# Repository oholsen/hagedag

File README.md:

# hagedag
DIY lawn mower robot

## Testing

Run unit tests:

    poetry run pytest -s

Run simulation:

    poetry run python .\record.py

(Replay log file, should add fail safe detection ++):

    poetry run python .\record.py .\data\burned-motor.log

## TODO

* motor burned (one wheel was tangled in grass):
  * wifi connection delayed - commands and feedback
  * figure out why robot estimate wrongly turned and why it did not recover when moving "right"
  * fix: move control to robot, detect connection delays, ignore delayed information, timestamp from STM32, use timestamp from GPS

* high load on motor detection - possibly integrate and average
  * cut in STM or in control? Control, as will get to know what is going on?
  * STM will stop robot if communication errors, safe to cut in control.
  * different max for instantaneous and average load?
  * Simply stop when above threshold (instantaneous)

* robot stuck detection: anomaly on prediction and GPS
  * measure distance travelled over last 5 say on GPS and compare to integrated speed

* wifi delay detection
    * shorter timeout (1s/2s)
    * embed timeout in command
    * alert in GUI

* stop cutter outside fence?
* cutter stuck detection
* revs sensor on cutter

* slow down near fence
* keep estimating position with odometer only when no GPS fix -> higher uncertainty

* Fence
    * increase area behind garage
    * reduce fence area near stairs

* App robustness
    * restart GPS service when USB unavailable, also ntrip client fails badly? restart service should be ok...
    * properly stop all tasks, also controld connection, from PC app
    * program firmware with heartbeat on commands

Usability:
    * Don't make PC app always be on top: run GUI task in own thread?
    * PC/Web/mobile app framework: pyplot, JS, plotly-dash, ...
    * identify what goes wrong / status
    * restart e.g. line scan from current position?

* Tidy up app:
   * remove unused code

* move app to robot

* change direction of robot

* slow down near fence, speed up in the middle (may make crash prediction below unnecessary - if reducing heartbeat timeout in robot)
* keep going for large HDOP if far from fence
* use GPS hdop in tracking, figure out why HDOP is 0.5 when RTK
* looser cut-off on no RTK - either adjust error in GPS tracking (check out HDOP in RMC)
 - or - accept no GPS for a while - at least if heading is good and is not going to crash.
 estimate time to impact from last good RTK position?
BUT: also quicker than 5s heartbeat timeout, i.e. direct STOP command if about to crash and loose RTK 
* avoid going in circles on drifting GPS: HDOP -> tracker could solve that
* area filling - scan lines
* if HDOP high: alternative targets or wait for ok HDOP
* fence bump control: reverse out from fence

* automatic charging
* docking garage
* camera
* camera coverage of garden
* realsense - mapping, collision avoidance

Mission control dashboard
- map (draw AOI, speeds/behavior, move fence, path, density, ..., GPS/tracking error, heading error)
- system health: show currents, battery level
- (E)stop button
- Duration, Ah drawn (total, trip (since charge), button for reset trip charge), distance covered
- Mode: fence bump, lines, manual, manual override (temporarily)
- Manual controls
- Start mission - which mission
- app to monitor status, with notifications on issues

Analytics
- GPS/tracking precision
- Coverage
- Replay/show mission on map

Mapping
- find fence - show position on map with manual control - recorder mode....

Mission control
- run to area of "little" probability
- speed and cut speed as fn(x,y)
- avoid tail swinging out (reverse back out, put GPS above cutter and turn around cutter)
- estimate error based on odometry and GPS signal - keep on going if looses RTK
- TODO: check GPS error when stopped and no RTK

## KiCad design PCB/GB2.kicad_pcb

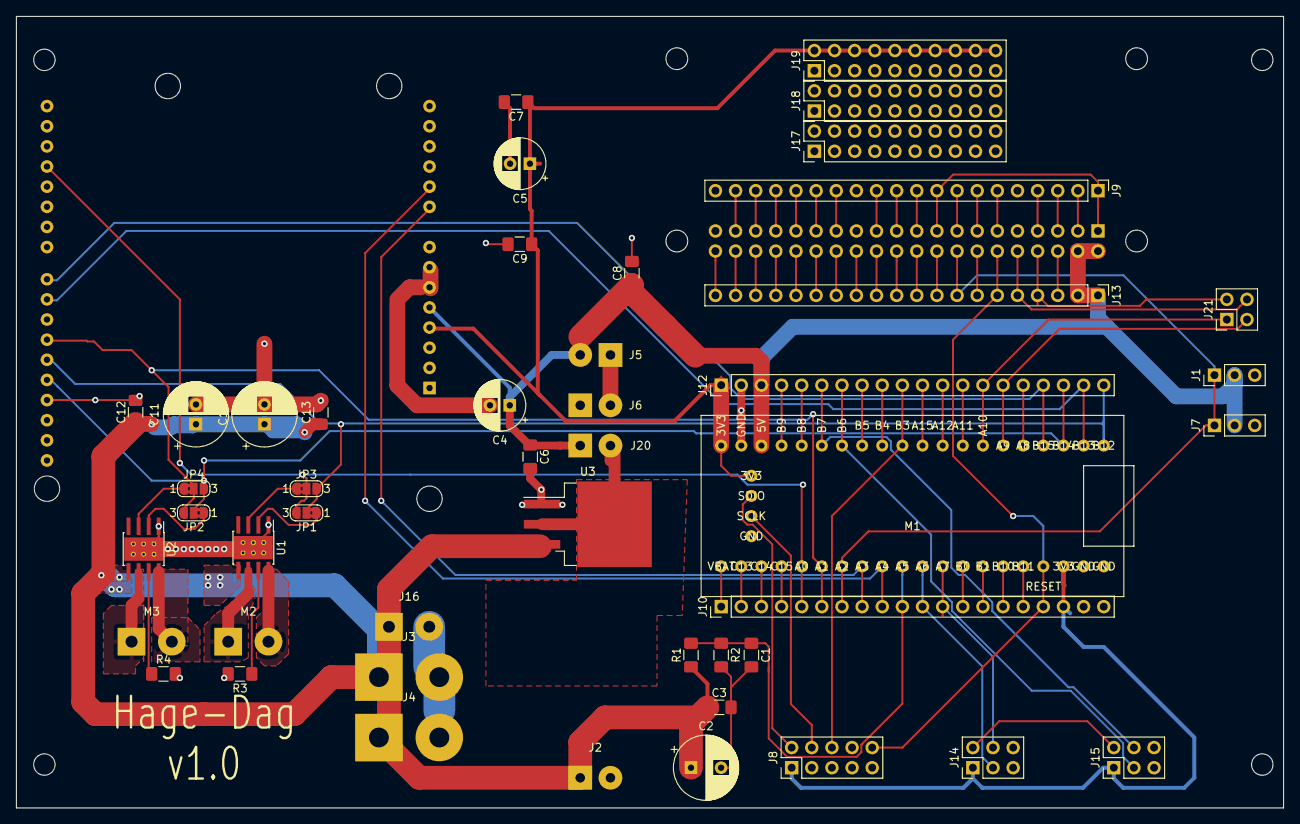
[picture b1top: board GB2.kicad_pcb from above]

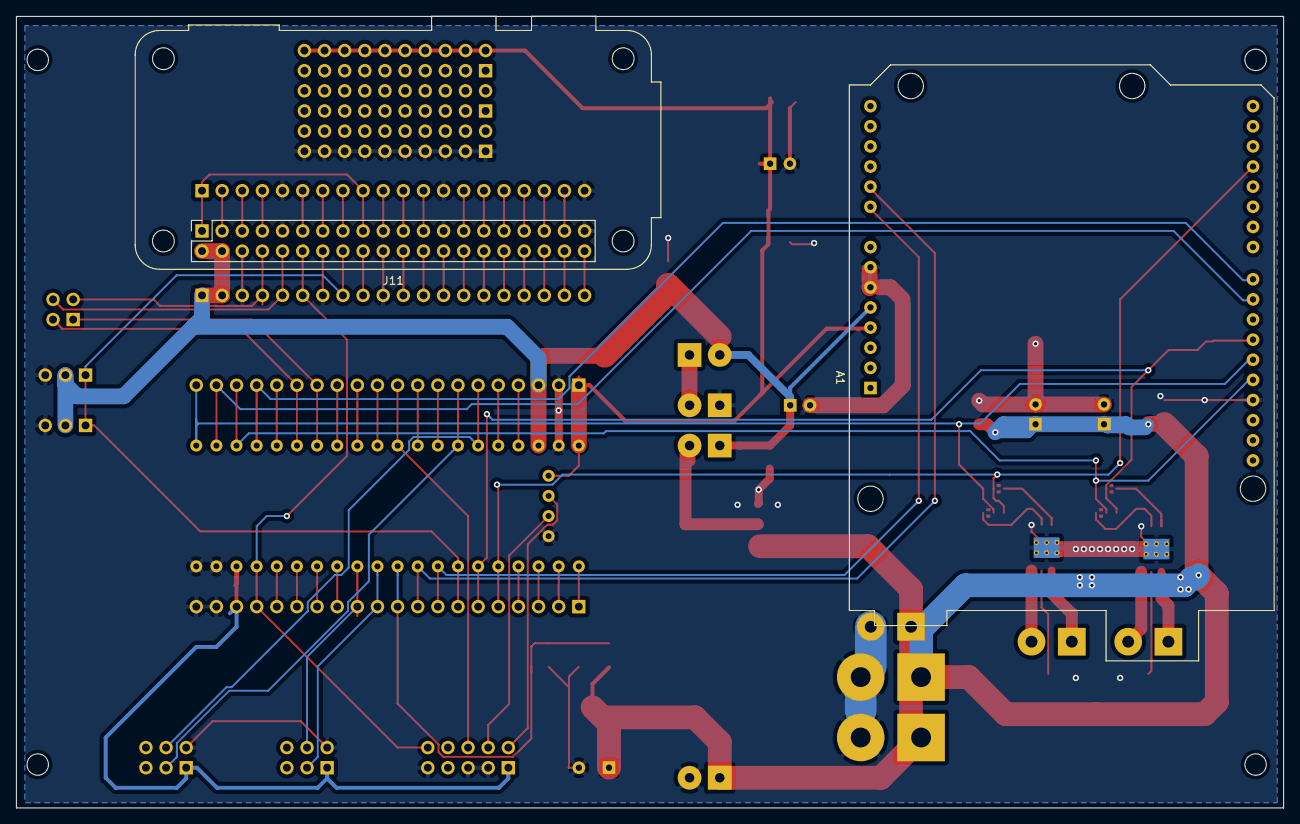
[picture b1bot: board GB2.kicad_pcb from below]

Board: 2 copper layers, 159.9 x 99.9 mm, 53 parts (2 on the bottom side), 79 nets.

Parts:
A1: Motor Shield; Arduino_UNO_R3_WithMountingHoles
C1, C3, C6, C7, C8, C9, C12, C13: C; C_1206_3216Metric_Pad1.42x1.75mm_HandSolder
C2: CP; CP_Radial_D8.0mm_P3.80mm
C4, C5: CP; CP_Radial_D6.3mm_P2.50mm
C10, C11: CP; CP_Radial_D8.0mm_P2.50mm
J1, J7: Cutter PWM; PinHeader_1x03_P2.54mm_Vertical
J2: BEC In; SolderWirePad_1x02_P3.81mm_Drill1.2mm
J3: Cutter; SolderWirePad_1x02_P7.62mm_Drill2.5mm
J4: Bat; SolderWirePad_1x02_P7.62mm_Drill2.5mm
J5: BEC; SolderWirePad_1x02_P3.81mm_Drill1.2mm
J6: BEC Out; SolderWirePad_1x02_P3.81mm_Drill1.2mm
J8: ARM; PinHeader_2x05_P2.54mm_Vertical
J9: RPi1; PinHeader_1x20_P2.54mm_Vertical
J10: STM2; PinHeader_1x20_P2.54mm_Vertical
J11: RPi; Raspberry_Pi_Zero_Socketed_THT_FaceDown_MountingHoles
J12: STM1; PinHeader_1x20_P2.54mm_Vertical
J13: RPi2; PinHeader_1x20_P2.54mm_Vertical
J14: Encoder A; PinHeader_2x03_P2.54mm_Vertical
J15: Encoder B; PinHeader_2x03_P2.54mm_Vertical
J16: Motors; SolderWirePad_1x02_P5.08mm_Drill1.5mm
J17, J18, J19: Proto; PinHeader_2x10_P2.54mm_Vertical
J20: VREG; SolderWirePad_1x02_P3.81mm_Drill1.2mm
J21: UART; PinHeader_2x02_P2.54mm_Vertical
JP1, JP2: IN2; SolderJumper-3_P1.3mm_Bridged2Bar12_RoundedPad1.0x1.5mm_Num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
JP3, JP4: IN1; SolderJumper-3_P1.3mm_Bridged2Bar12_RoundedPad1.0x1.5mm_Num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
M1: STM; STM-Nano
M2, M3: Motor_DC; SolderWirePad_1x02_P5.08mm_Drill1.5mm
MK1, MK2, MK3, MK4: Mounting_Hole_PAD; MountingHole_2.7mm
R1, R2, R3, R4: R; R_1206_3216Metric_Pad1.42x1.75mm_HandSolder
U1, U2: DRV8872DDA; Texas_HTSOP-8-1EP_3.9x4.9mm_P1.27mm_EP2.95x4.9mm_Mask2.4x3.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
U3: 5V; TO-263-3_TabPin2

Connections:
+3V3: A1.4, C5.1, C7.1, C9.1, J8.1, J10.18, J12.1, J14.1, J15.1, J19.2, J19.4, J19.6, J19.8, J19.10, J19.12, J19.14, J19.16, J19.18, J19.20, M1.1, M1.23, M1.44
+5V: A1.5, C4.1, C6.1, C8.1, J1.2, J5.2, J7.2, J11.2, J11.4, J12.3, J13.1, J13.2, J20.1, M1.3
+BATT: C2.1, C3.1, C10.1, C11.1, C12.1, C13.1, J2.1, J3.1, J4.1, J16.1, R1.1, U1.5, U2.5, U3.3
/BrakeA: A1.24, J12.19, M1.19
/BrakeB: A1.23, J12.17, M1.17
/EncA1: J10.11, J14.3, M1.30
/EncA2: J10.12, J14.4, M1.29
/EncB1: J12.7, J15.3, M1.7
/EncB2: J12.6, J15.4, M1.6
/PI_RX: J11.10, J13.5, J21.4
/PI_TX: J11.8, J13.4, J21.2
/PWMC: J1.1, J7.1, J10.7, J11.16, J13.8, M1.34
/Reset: J8.10, J10.17, J11.12, J13.6, M1.24
/STM_RX: J12.14, J21.1, M1.14
/STM_TX: J12.15, J21.3, M1.15
/SenseA: A1.9, J10.8, M1.33
/SenseB: A1.10, J10.9, M1.32
/VBAT_ADC: C1.1, J10.10, M1.31, R1.2, R2.1
/VREG: J20.2, U3.2
DIRA: A1.27, J12.20, JP1.2, JP3.3, M1.20
DIRB: A1.28, J12.18, JP2.2, JP4.3, M1.18
GND: A1.6, A1.7, A1.29, C1.2, C2.2, C3.2, C4.2, C5.2, C6.2, C7.2, C8.2, C9.2, C10.2, C11.2, C12.2, C13.2, J1.3, J2.2, J3.2, J4.2, J6.1, J7.3, J8.3, J8.5, J8.9, J9.5, J9.13, J9.20, J10.19, J10.20, J11.6, J11.9, J11.14, J11.20, J11.25, J11.30, J11.34, J11.39, J12.2, J13.3, J13.7, J13.10, J13.15, J13.17, J14.2, J15.2, J16.2, J17.1, J17.3, J17.5, J17.7, J17.9, J17.11, J17.13, J17.15, J17.17, J17.19, M1.2, M1.21, M1.22, M1.41, R2.2, R3.2, R4.2, U1.1, U1.9, U2.1, U2.9, U3.1
unnamed: J5.1, J6.2
unnamed: J8.2, M1.43
unnamed: J8.4, M1.42
unnamed: J10.1, M1.40
unnamed: J10.2, M1.39
unnamed: J10.3, M1.38
unnamed: J10.4, M1.37
unnamed: J10.13, M1.28
unnamed: J10.14, M1.27
unnamed: J10.15, M1.26
unnamed: J10.16, M1.25
unnamed: J9.1, J9.9, J11.1, J11.17
unnamed: J9.2, J11.3
unnamed: J9.3, J11.5
unnamed: J9.4, J11.7
unnamed: J9.6, J11.11
unnamed: J9.7, J11.13
unnamed: J9.8, J11.15
unnamed: J11.18, J13.9
unnamed: J9.10, J11.19
unnamed: J9.11, J11.21
unnamed: J11.22, J13.11
unnamed: J9.12, J11.23
unnamed: J11.24, J13.12
unnamed: J11.26, J13.13
unnamed: J9.14, J11.27
unnamed: J11.28, J13.14
unnamed: J9.15, J11.29
unnamed: J9.16, J11.31
unnamed: J11.32, J13.16
unnamed: J9.17, J11.33
unnamed: J9.18, J11.35
unnamed: J11.36, J13.18
unnamed: J9.19, J11.37
unnamed: J11.38, J13.19
unnamed: J11.40, J13.20
unnamed: J12.4, M1.4
unnamed: J12.5, M1.5
unnamed: J12.8, M1.8
unnamed: J12.9, M1.9
unnamed: J8.6, J12.10, M1.10
unnamed: J12.11, M1.11
unnamed: J12.12, M1.12
unnamed: J12.13, M1.13
unnamed: J12.16, M1.16
unnamed: JP1.1, U1.2
unnamed: JP2.1, U2.2
unnamed: JP3.1, U1.3
unnamed: JP4.1, U2.3
unnamed: M2.1, U1.6
unnamed: M2.2, U1.8
unnamed: M3.1, U2.6
unnamed: M3.2, U2.8
unnamed: R3.1, U1.7
unnamed: R4.1, U2.7
PWMA: A1.18, J10.5, JP1.3, JP3.2, M1.36
PWMB: A1.26, J10.6, JP2.3, JP4.2, M1.35

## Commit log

2019-08-17 Working prototype of keeping the robot in a box
2019-08-17 RPi code: dead ugly web GUI and control via web socket
2019-08-17 Add PCB project for KiCad
2019-08-17 Filter blob area
2019-08-17 Cleanup
2019-08-17 Test downsample effect on speed: no effect
2019-08-17 Move npm into gui
2019-08-17 Add option to disable heartbeat (for multiple controls)
2019-08-18 Use biggest blob subject to constraints as position
    Constraints:
    - area range
    - inside AOI
2019-08-18 Use config file, color dump on mouse click in "frame"
2019-08-25 More configuration, improved control
2019-08-28 Ellipse test for disk
2019-09-07 Guard against division by zero when no ellipse
2019-09-07 ignore files
2019-09-07 Simplify GUI
2019-09-07 Reconnect websocket
2019-09-07 Add Cut0 button, also stop STM on RPi heartbeat timeout
2019-09-07 Fix battery and heartbeat
2019-09-14 Motion tracking and optical flow tests
2019-09-14 Options to disable robot control and inside timeout
    Both should disabled under manual control
2019-09-14 Right click for logging fence points
2019-09-15 Filter commands with robot.control config
2019-09-15 Use adaptive background subtraction
2019-09-15 Create ROI outside background subtraction
2019-09-15 Factor out old processing and use diff.process2()
    Create ROI from fence before first frame
2019-09-15 Motion tracking
2019-09-15 Remove unused code
    Handle events also on frames without position
2019-09-23 Use reversible cutter
2019-09-23 Halve range for turn
2019-09-23 remove debug print
2019-09-24 Python 3.5 with asyncio and logging
2020-03-06 Simulate line control
2020-03-07 Add PID control
2020-04-12 Add firmware for STM32 controller
2020-04-21 Refactor simulation
2020-04-28 WIP: state estimation for getting heading to control robot
2020-04-29 Add GPS service with TCP broadcast server and NTRIP client for RTK
2020-05-01 Estimate heading with EKF
2020-05-01 Tune, fix, and simplify
2020-05-02 Tracking and control of robot in real-time, record and play, and simulation
2020-05-03 Align coordinate system with garden
2020-05-03 Add robot commands
2020-05-03 Move video processing and control
2020-05-03 Use brushed motor cutter
2020-05-04 Remove closed connections
2020-05-04 Working horizontal line control
    Roughly +-10 cm vertical error
2020-05-16 Use brushless cutter motor again. Stop command does not stop cutter.
2020-05-16 WIP: current measurement
2020-05-16 Output Revs in correct order
2020-05-21 Measure currents
2020-05-22 Working naiive fence bump control
    - filter on RTK fix
2020-05-25 Point control simulation
2020-05-26 Working fence bump simulation
2020-05-26 Fix heartbeat timeout
2020-05-27 Real fence bump control
2020-05-31 Mission config, HDOP filter, filter GPS msgs, battery cut-off
2020-05-31 Cutter interface and selection in one place
2020-05-31 Graceful degradation on current measurement failure
2020-05-31 Avoid insane memory usage: clear log on every IV report
2020-06-01 Working horizontal line scan within box
2020-06-03 Show all of grass
2020-06-03 Feed observation error to tracker
2020-06-03 More overlap on scan lines
2020-06-06 Simulate mission
2020-06-07 Add fence shrink control
    Reduce speed near end point
2020-06-07 Tune garden fence
2020-06-08 Send single error message on current measurement
2020-06-09 Add replay and gracefully exit fence shrink control
2020-06-10 Better arc and point control
    A little cleanup
2020-06-16 Catch exceptions in controld read/write tasks in order to reconnect
2020-06-16 Add LineControl, reduce speed near target, tighter track control
2020-06-18 Shrink fence with path/line controls
    Path planning between multiple areas
2020-06-18 Keep battery low condition
    Avoids draining battery very low on numerous restarts - should measure battery low when motors run.
2020-06-18 Tune garden and mission
2020-06-18 WIP: ws server for JS GUI.
2020-06-26 Web GUI prototype
2020-06-26 Add origin, cleanup
2020-06-28 Use GGA to get HDOP
2020-06-28 Tune LineControl
2020-06-28 Adjust fence
2020-06-29 add log
2020-06-30 Fix replay
2020-07-03 set up poetry
2020-07-03 Parse GPS time as datetime.time
2020-07-05 WIP: "m" command with timeout, report STM32 time
2020-07-05 Refactor play.process()
2020-07-05 Change to "move" command with timeout
    Basis for round-trip delay handling
    Removed heartbeat and independent speed/turn commands
2020-07-05 Record STM32 time
2020-07-18 Bump lodash from 4.17.15 to 4.17.19 in /raspberry/gui
    Bumps [lodash](https://github.com/lodash/lodash) from 4.17.15 to 4.17.19.
    - [Release notes](https://github.com/lodash/lodash/releases)
    - [Commits](https://github.com/lodash/lodash/compare/4.17.15...4.17.19)
2020-07-22 WIP: power high fail safe
2020-07-22 Refactor, stop sending heartbeat, send new Move message
2020-08-04 Fixes for ScanHLine control
2020-08-06 Remove tracking from RobotState
2020-08-06 Rename record.py to main.py
2020-08-08 Motor control by ticks/s
2020-08-08 Rotation is positive anticlockwise from above
2020-08-08 Robot uses ticks/s, add Status with overload flag
2020-08-08 Use speed, omega from mission in ScanHLine
2020-08-08 Fix omega on arc in ScanHLine
2020-08-19 remove security warnings
2020-08-20 Remove spaces in Power message
2020-08-20 Add Status and Power and cut heartbeat
2020-08-20 Set 5s timeout on CUT command
2020-08-20 Fixes for new protocol, use Status message to detect overload
2020-08-26 pubsub experiment
2020-08-26 Cleanup and doc, include some thinking around holes
2020-09-02 Bump bl from 4.0.2 to 4.0.3 in /raspberry/gps
    Bumps [bl](https://github.com/rvagg/bl) from 4.0.2 to 4.0.3.
    - [Release notes](https://github.com/rvagg/bl/releases)
    - [Commits](https://github.com/rvagg/bl/compare/v4.0.2...v4.0.3)
2020-09-17 Back to brushed cutter
2020-09-22 Factor out tests
2020-09-22 Raise threshold and integration time for power overload
2025-03-28 Bump tar-fs from 2.0.1 to 2.1.2 in /raspberry/gps
    Bumps [tar-fs](https://github.com/mafintosh/tar-fs) from 2.0.1 to 2.1.2.
    - [Commits](https://github.com/mafintosh/tar-fs/compare/v2.0.1...v2.1.2)
    ---
    updated-dependencies:
    - dependency-name: tar-fs
    dependency-type: indirect
2025-06-03 Bump tar-fs from 2.0.1 to 2.1.3 in /raspberry/gps
    Bumps [tar-fs](https://github.com/mafintosh/tar-fs) from 2.0.1 to 2.1.3.
    - [Commits](https://github.com/mafintosh/tar-fs/commits)
    ---
    updated-dependencies:
    - dependency-name: tar-fs
    dependency-version: 2.1.3
2025-09-24 Bump tar-fs from 2.0.1 to 2.1.4 in /raspberry/gps
    Bumps [tar-fs](https://github.com/mafintosh/tar-fs) from 2.0.1 to 2.1.4.
    - [Commits](https://github.com/mafintosh/tar-fs/compare/v2.0.1...v2.1.4)
    ---
    updated-dependencies:
    - dependency-name: tar-fs
    dependency-version: 2.1.4
2025-11-18 Bump js-yaml from 3.13.1 to 3.14.2 in /raspberry/gps
    Bumps [js-yaml](https://github.com/nodeca/js-yaml) from 3.13.1 to 3.14.2.
    - [Changelog](https://github.com/nodeca/js-yaml/blob/master/CHANGELOG.md)
    - [Commits](https://github.com/nodeca/js-yaml/compare/3.13.1...3.14.2)
    ---
    updated-dependencies:
    - dependency-name: js-yaml
2026-02-04 Bump semver from 5.7.1 to 5.7.2 in /raspberry/gps
    Bumps [semver](https://github.com/npm/node-semver) from 5.7.1 to 5.7.2.
    - [Release notes](https://github.com/npm/node-semver/releases)
    - [Changelog](https://github.com/npm/node-semver/blob/v5.7.2/CHANGELOG.md)
    - [Commits](https://github.com/npm/node-semver/compare/v5.7.1...v5.7.2)
    ---
    updated-dependencies:
